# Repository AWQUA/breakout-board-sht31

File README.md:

# breakout-board-sht31

### This repo contains the schematic and board layout for a simple and effective air temperature and humidity sensor.

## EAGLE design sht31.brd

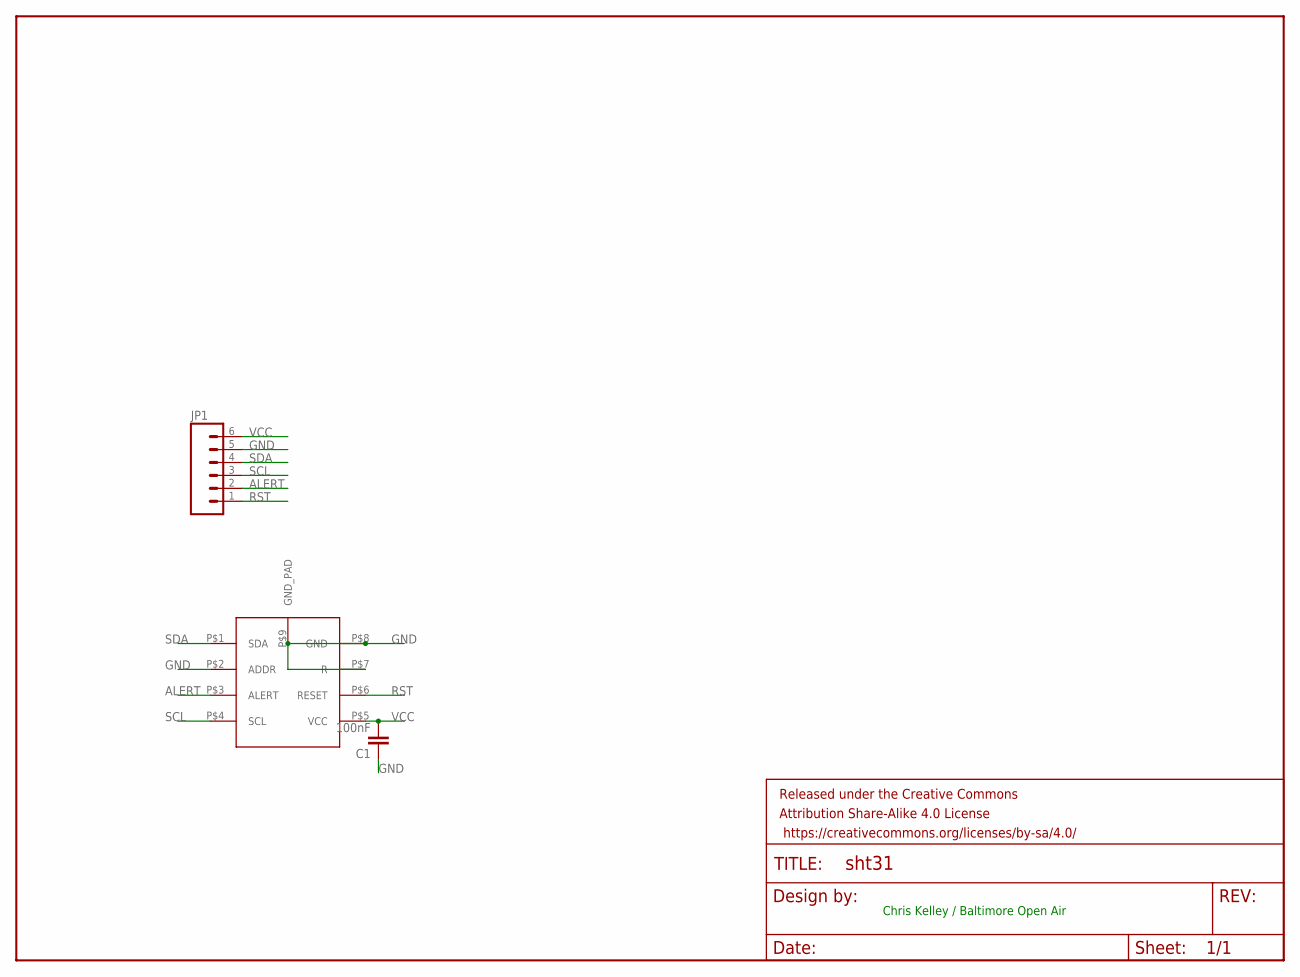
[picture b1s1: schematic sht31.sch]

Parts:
C1: 100nF; 0603-CAP
FRAME1: FRAME-LETTER; CREATIVE_COMMONS
JP1: M06SILK_FEMALE_PTH; 1X06
U$1: SHT31-D

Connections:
ALERT: JP1.2, U$1.P$3 (ALERT)
GND: C1.1, JP1.5, U$1.P$2 (ADDR), U$1.P$7 (R), U$1.P$8 (GND), U$1.P$9 (GND_PAD)
RST: JP1.1, U$1.P$6 (RESET)
SCL: JP1.3, U$1.P$4 (SCL)
SDA: JP1.4, U$1.P$1 (SDA)
VCC: C1.2, JP1.6, U$1.P$5 (VCC)

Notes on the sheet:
Chris Kelley / Baltimore Open Air

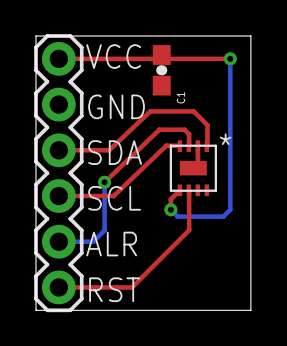
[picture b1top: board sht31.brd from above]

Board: 2 copper layers, 11.9 x 15.2 mm, 4 parts (0 on the bottom side), 6 nets.

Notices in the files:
parts and their libraries:
SparkFun-Passives: Licensing: Creative Commons ShareAlike 4.0 International - https://creativecommons.org/licenses/by-sa/4.0
SparkFun-Aesthetics: Released under the Creative Commons Attribution Share-Alike 4.0 License
SparkFun-Aesthetics: https://creativecommons.org/licenses/by-sa/4.0
